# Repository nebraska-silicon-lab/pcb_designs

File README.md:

# PCB Designs for Silicon Lab

This repository contains design and related work for printed circuit boards used in Silicon Lab activites.

To edit these boards, install [Kicad](http://kicad-pcb.org/). Each design should have an PNG image of the most recent iteration of the design. This makes it easier to view the boards without needing to download and install Kicad.

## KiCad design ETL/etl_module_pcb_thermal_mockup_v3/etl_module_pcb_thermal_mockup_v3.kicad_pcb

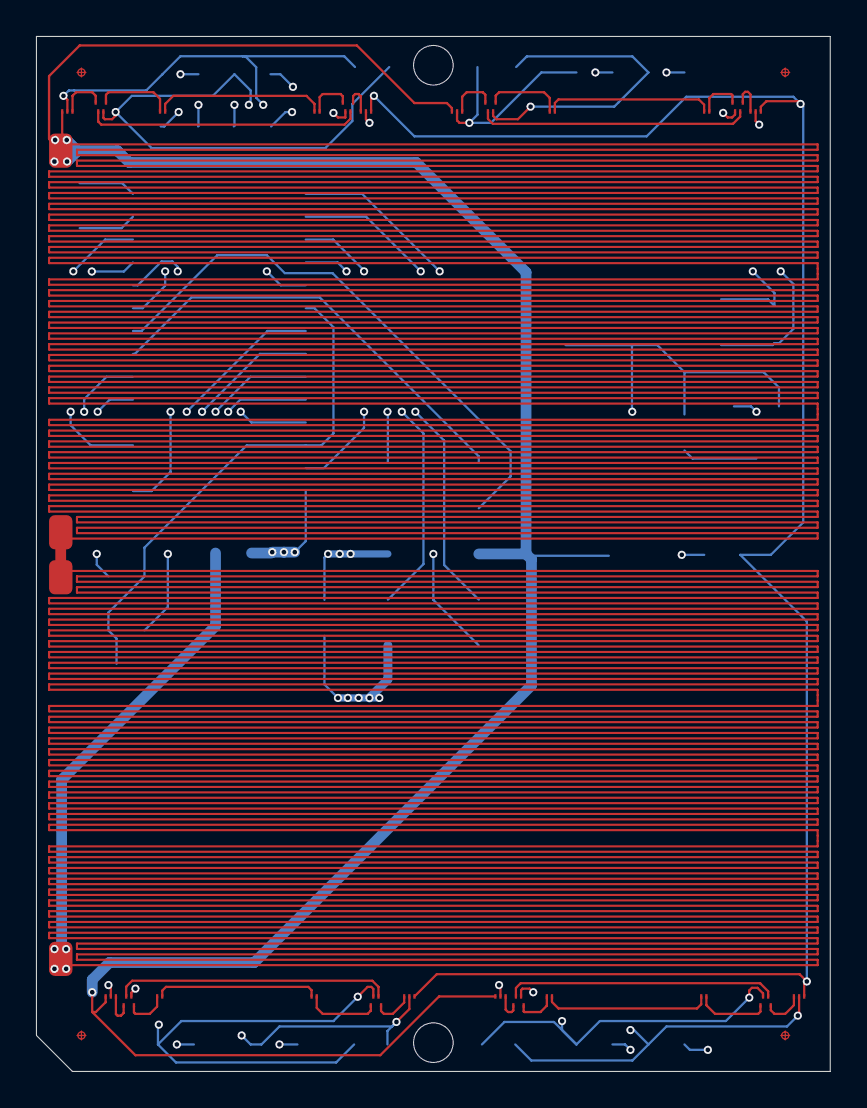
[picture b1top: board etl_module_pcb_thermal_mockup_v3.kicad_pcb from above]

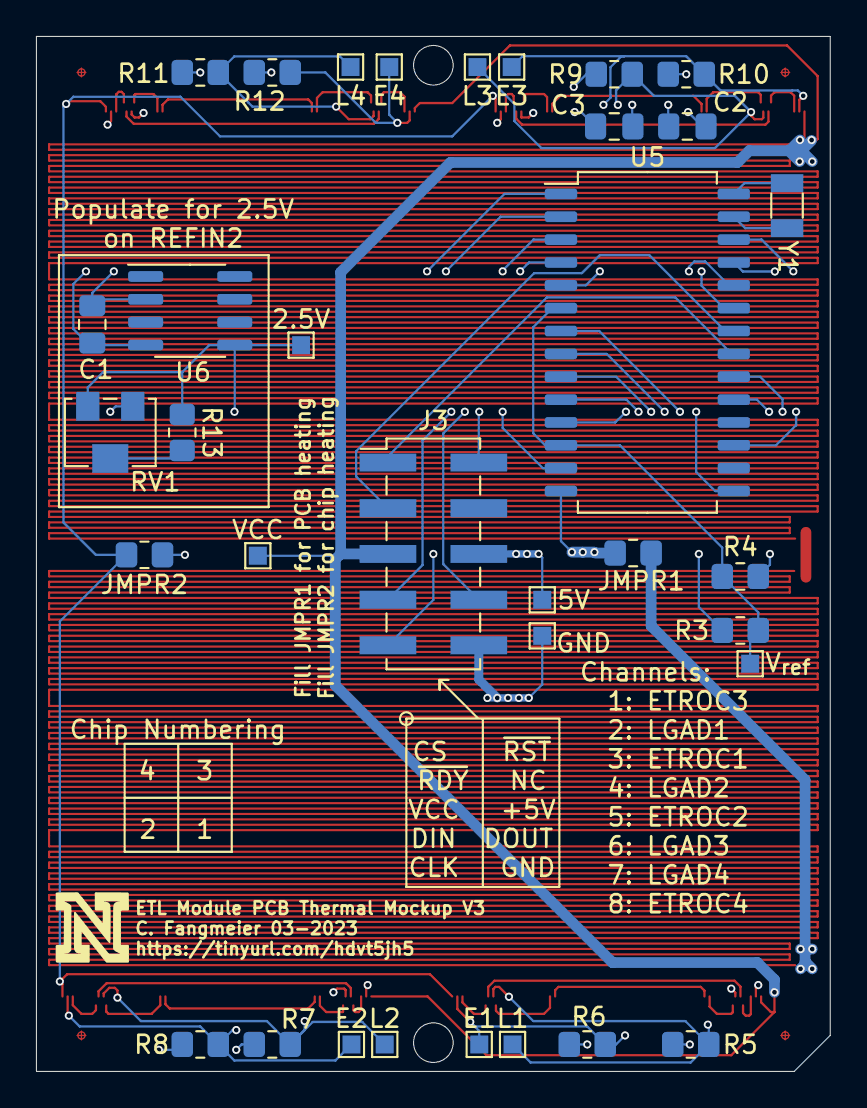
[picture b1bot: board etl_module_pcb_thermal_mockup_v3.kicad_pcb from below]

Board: 4 copper layers, 44.1 x 57.5 mm, 40 parts (34 on the bottom side), 49 nets.

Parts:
2.5V, 5V: TestPoint; TestPoint_Pad_1.0x1.0mm
C1: 1uF; C_0805_2012Metric_Pad1.18x1.45mm_HandSolder
C2: 0.1uF; C_0805_2012Metric_Pad1.18x1.45mm_HandSolder
C3: 10 uF; C_0805_2012Metric_Pad1.18x1.45mm_HandSolder
E1, E2, E3, E4: TestPoint; TestPoint_Pad_1.0x1.0mm
GND: TestPoint; TestPoint_Pad_1.0x1.0mm
J3: Conn_02x05_Counter_Clockwise; PinHeader_2x05_P2.54mm_Vertical_SMD
JMPR1, JMPR2: 0; R_0805_2012Metric_Pad1.20x1.40mm_HandSolder
L1, L2, L3, L4: TestPoint; TestPoint_Pad_1.0x1.0mm
R1, R2: 12.6; ETROC_Heater_Serpantine
R3, R4, R5, R6, R7, R8, R9, R10, R11, R12: 40k; R_0805_2012Metric_Pad1.20x1.40mm_HandSolder
R13: 1M; R_0805_2012Metric_Pad1.20x1.40mm_HandSolder
RV1: 25k; Potentiometer_Bourns_3224W_Vertical
U1, U2, U3, U4: ETROC_dummy_thermal_sensors; PCB_ETROC2_dummy
U5: AD77x8; SOIC-28W_7.5x18.7mm_P1.27mm
U6: AD780; SOIC-8_3.9x4.9mm_P1.27mm
VCC: TestPoint; TestPoint_Pad_1.0x1.0mm
V_{ref}: TestPoint; TestPoint_Pad_1.0x1.0mm
Y1: 32kHz; Crystal_SMD_3215-2Pin_3.2x1.5mm

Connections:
+5V: 5V.1, C1.1, C2.1, C3.1, J3.6, R3.1, R5.1, R6.1, R7.1, R8.1, R9.1, R10.1, R11.1, R12.1, U5.3 (AV_{DD}), U5.26 (DV_{DD}), U6.2 (+V_{IN})
/2.5V: 2.5V.1, R13.1, RV1.3, U5.13 (REFIN2(+)/AIN9), U6.5 (TRIM)
/CLK: J3.9, U5.20 (SCLK)
/CS: J3.1, U5.21 (~CS)
/DIN: J3.7, U5.24 (DIN)
/DOUT: J3.8, U5.23 (DOUT)
/ETROC1: E1.1, R6.2, U1.119 (ETROC_BR-), U5.9 (AIN3)
/ETROC2: E2.1, R8.2, U2.119 (ETROC_BR-), U5.11 (AIN5)
/ETROC3: E3.1, R10.2, U3.119 (ETROC_BR-), U5.7 (AIN1)
/ETROC4: E4.1, R12.2, U4.119 (ETROC_BR-), U5.2 (AIN8)
/LGAD1: L1.1, R5.2, U1.105 (LGAD_BR-), U5.8 (AIN2)
/LGAD2: L2.1, R7.2, U2.105 (LGAD_BR-), U5.10 (AIN4)
/LGAD3: L3.1, R9.2, U3.105 (LGAD_BR-), U5.15 (AIN6)
/LGAD4: L4.1, R11.2, U4.105 (LGAD_BR-), U5.1 (AIN7)
/VSS: JMPR2.2, U1.121 (VSS), U2.121 (VSS), U3.1 (VCC), U4.1 (VCC)
/V_{ref}: R3.2, R4.1, U5.6 (REFIN1(+)), U5.12 (AINCOM), V_{ref}.1
/~RDY: J3.3, U5.22 (~RDY)
/~RESET: J3.2, U5.19 (~RESET)
GND: C1.2, C2.2, C3.2, GND.1, J3.10, JMPR1.2, JMPR2.1, R4.2, RV1.1, U1.3 (ETROC_BLp), U1.11 (LGAD_BL+), U2.3 (ETROC_BLp), U2.11 (LGAD_BL+), U3.3 (ETROC_BLp), U3.11 (LGAD_BL+), U4.3 (ETROC_BLp), U4.11 (LGAD_BL+), U5.4 (AGND), U5.5 (REFIN1(-)), U5.14 (REFIN2(-)/AIN10), U5.17 (AGND), U5.25 (DGND), U6.4 (GND)
unnamed: JMPR1.1, R2.2
unnamed: R1.2, R2.1
unnamed: R13.2, RV1.2
unnamed: U1.5 (ETROC_BL-), U1.8 (ETROC_TL+)
unnamed: U1.12 (LGAD_BL-), U1.21 (LGAD_TL+)
unnamed: U1.23 (LGAD_TL-), U1.81 (LGAD_TR+)
unnamed: U1.83 (LGAD_TR-), U1.104 (LGAD_BR+)
unnamed: U1.9 (ETROC_TL-), U1.107 (ETROC_TR+)
unnamed: U1.108 (ETROC_TR-), U1.117 (ETROC_BR+)
unnamed: U2.5 (ETROC_BL-), U2.8 (ETROC_TL+)
unnamed: U2.12 (LGAD_BL-), U2.21 (LGAD_TL+)
unnamed: U2.23 (LGAD_TL-), U2.81 (LGAD_TR+)
unnamed: U2.83 (LGAD_TR-), U2.104 (LGAD_BR+)
unnamed: U2.9 (ETROC_TL-), U2.107 (ETROC_TR+)
unnamed: U2.108 (ETROC_TR-), U2.117 (ETROC_BR+)
unnamed: U3.5 (ETROC_BL-), U3.8 (ETROC_TL+)
unnamed: U3.12 (LGAD_BL-), U3.21 (LGAD_TL+)
unnamed: U3.23 (LGAD_TL-), U3.81 (LGAD_TR+)
unnamed: U3.83 (LGAD_TR-), U3.104 (LGAD_BR+)
unnamed: U3.9 (ETROC_TL-), U3.107 (ETROC_TR+)
unnamed: U3.108 (ETROC_TR-), U3.117 (ETROC_BR+)
unnamed: U4.5 (ETROC_BL-), U4.8 (ETROC_TL+)
unnamed: U4.12 (LGAD_BL-), U4.21 (LGAD_TL+)
unnamed: U4.23 (LGAD_TL-), U4.81 (LGAD_TR+)
unnamed: U4.83 (LGAD_TR-), U4.104 (LGAD_BR+)
unnamed: U4.9 (ETROC_TL-), U4.107 (ETROC_TR+)
unnamed: U4.108 (ETROC_TR-), U4.117 (ETROC_BR+)
unnamed: U5.27 (XTAL2), Y1.1
unnamed: U5.28 (XTAL1), Y1.2
VCC: J3.5, R1.1, U1.1 (VCC), U2.1 (VCC), U3.121 (VSS), U4.121 (VSS), VCC.1

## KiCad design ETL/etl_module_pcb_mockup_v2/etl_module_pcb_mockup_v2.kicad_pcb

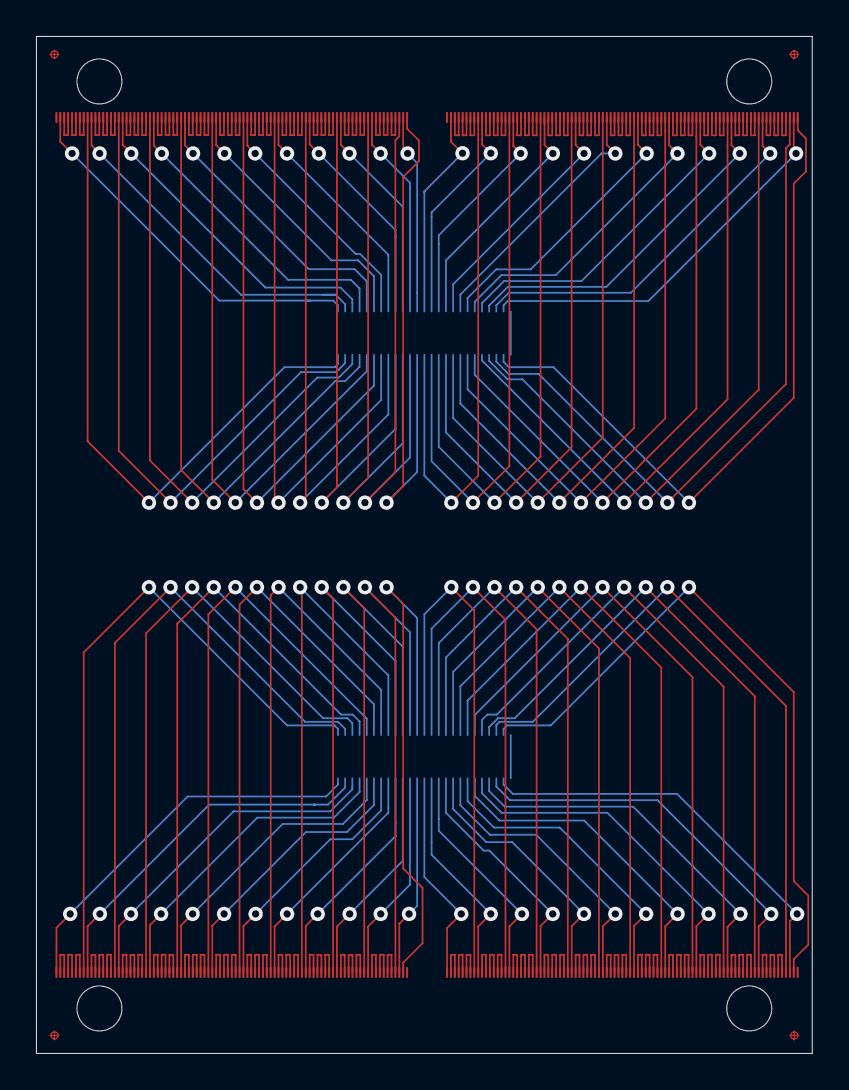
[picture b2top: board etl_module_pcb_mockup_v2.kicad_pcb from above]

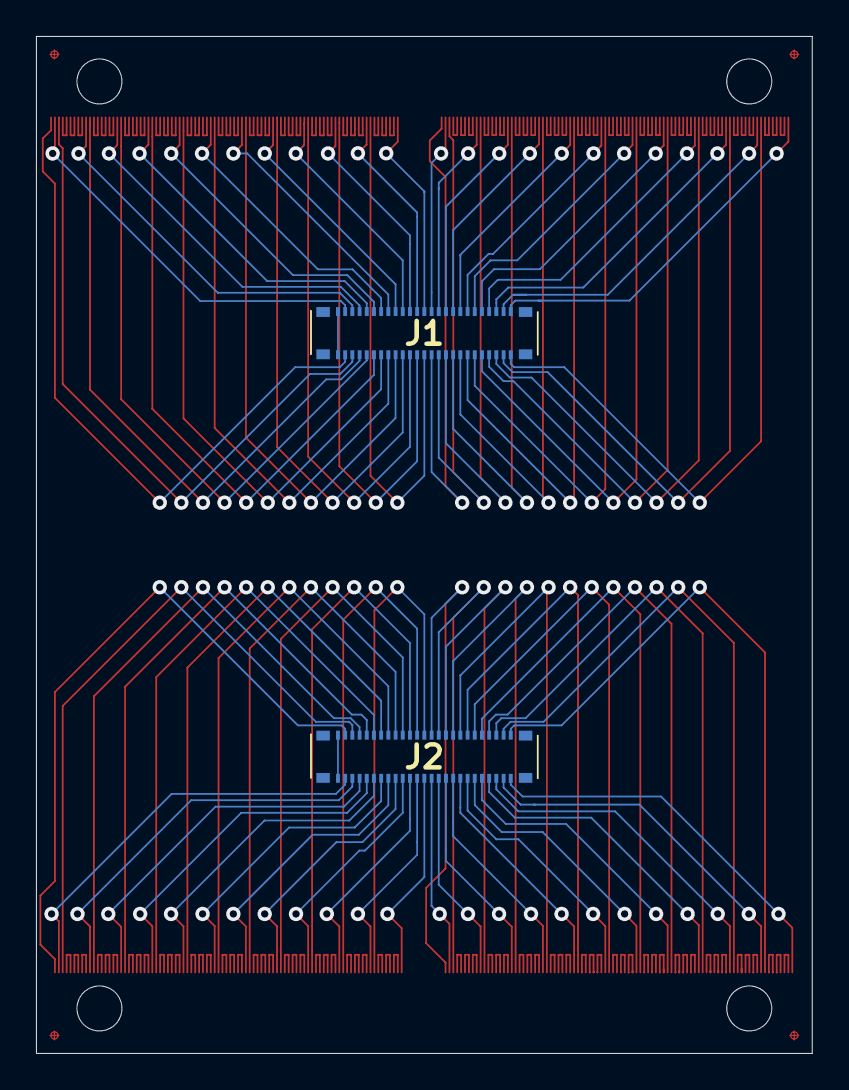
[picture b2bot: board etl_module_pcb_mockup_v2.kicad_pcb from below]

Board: 2 copper layers, 43.1 x 56.5 mm, 6 parts (2 on the bottom side), 230 nets.

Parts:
J1, J2: WP7B-S050VA1-R8000; WP7BS050VA1R8000
J3, J4, J5, J6: ETROC_91pad; ETROC_91pad_120x200um_216p44um_pitch

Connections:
/01_N: J2.1, J5.8
/01_P: J2.2, J5.1
/02_N: J2.3, J5.16
/02_P: J2.4, J5.9
/03_N: J2.5, J5.24
/03_P: J2.6, J5.17
/04_N: J2.7, J5.32
/04_P: J2.8, J5.25
/05_N: J2.9, J5.40
/05_P: J2.10, J5.33
/06_N: J2.11, J5.48
/06_P: J2.12, J5.41
/07_N: J2.13, J5.56
/07_P: J2.14, J5.49
/08_N: J2.15, J5.64
/08_P: J2.16, J5.57
/09_N: J2.17, J5.72
/09_P: J2.18, J5.65
/10_N: J2.19, J5.80
/10_P: J2.20, J5.73
/11_N: J2.21, J5.88
/11_P: J2.22, J5.81
/12_N: J2.23, J5.90
/12_P: J2.24, J5.89
/13_N: J2.25, J6.8
/13_P: J2.26, J6.1
/14_N: J2.27, J6.16
/14_P: J2.28, J6.9
/15_N: J2.29, J6.24
/15_P: J2.30, J6.17
/16_N: J2.31, J6.32
/16_P: J2.32, J6.25
/17_N: J2.33, J6.40
/17_P: J2.34, J6.33
/18_N: J2.35, J6.48
/18_P: J2.36, J6.41
/19_N: J2.37, J6.56
/19_P: J2.38, J6.49
/20_N: J2.39, J6.64
/20_P: J2.40, J6.57
/21_N: J2.41, J6.72
/21_P: J2.42, J6.65
/22_N: J2.43, J6.80
/22_P: J2.44, J6.73
/23_N: J2.45, J6.88
/23_P: J2.46, J6.81
/24_N: J2.47, J6.90
/24_P: J2.48, J6.89
/26_N: J1.2, J3.9
/26_P: J1.1, J3.2
/27_N: J1.4, J3.17
/27_P: J1.3, J3.10
/28_N: J1.6, J3.25
/28_P: J1.5, J3.18
/29_N: J1.8, J3.33
/29_P: J1.7, J3.26
/30_N: J1.10, J3.41
/30_P: J1.9, J3.34
/31_N: J1.12, J3.49
/31_P: J1.11, J3.42
/32_N: J1.14, J3.57
/32_P: J1.13, J3.50
/33_N: J1.16, J3.65
/33_P: J1.15, J3.58
/34_N: J1.18, J3.73
/34_P: J1.17, J3.66
/35_N: J1.20, J3.81
/35_P: J1.19, J3.74
/36_N: J1.22, J3.89
/36_P: J1.21, J3.82
/37_N: J1.24, J3.91
/37_P: J1.23, J3.90
/38_N: J1.26, J4.9
/38_P: J1.25, J4.2
/39_N: J1.28, J4.17
/39_P: J1.27, J4.10
/40_N: J1.30, J4.25
/40_P: J1.29, J4.18
/41_N: J1.32, J4.33
/41_P: J1.31, J4.26
/42_N: J1.34, J4.41
/42_P: J1.33, J4.34
/43_N: J1.36, J4.49
/43_P: J1.35, J4.42
/44_N: J1.38, J4.57
/44_P: J1.37, J4.50
/45_N: J1.40, J4.65
/45_P: J1.39, J4.58
/46_N: J1.42, J4.73
/46_P: J1.41, J4.66
/47_N: J1.44, J4.81
/47_P: J1.43, J4.74
/48_N: J1.46, J4.89
/48_P: J1.45, J4.82
/49_N: J1.48, J4.91
/49_P: J1.47, J4.90
/S1: J2.49, J2.50
/S2: J1.49, J1.50
unnamed: J3.3, J3.4
unnamed: J3.5, J3.6
unnamed: J3.7, J3.8
unnamed: J3.11, J3.12
unnamed: J3.13, J3.14
unnamed: J3.15, J3.16
unnamed: J3.19, J3.20
unnamed: J3.21, J3.22
unnamed: J3.23, J3.24
unnamed: J3.27, J3.28
unnamed: J3.29, J3.30
unnamed: J3.31, J3.32
unnamed: J3.35, J3.36
unnamed: J3.37, J3.38
unnamed: J3.39, J3.40
unnamed: J3.43, J3.44
unnamed: J3.45, J3.46
unnamed: J3.47, J3.48
unnamed: J3.51, J3.52
unnamed: J3.53, J3.54
unnamed: J3.55, J3.56
unnamed: J3.59, J3.60
unnamed: J3.61, J3.62
unnamed: J3.63, J3.64
unnamed: J3.67, J3.68
unnamed: J3.69, J3.70
unnamed: J3.71, J3.72
unnamed: J3.75, J3.76
unnamed: J3.77, J3.78
unnamed: J3.79, J3.80
unnamed: J3.83, J3.84
unnamed: J3.85, J3.86
unnamed: J3.87, J3.88
unnamed: J4.3, J4.4
unnamed: J4.5, J4.6
unnamed: J4.7, J4.8
unnamed: J4.11, J4.12
unnamed: J4.13, J4.14
unnamed: J4.15, J4.16
unnamed: J4.19, J4.20
unnamed: J4.21, J4.22
unnamed: J4.23, J4.24
unnamed: J4.27, J4.28
unnamed: J4.29, J4.30
unnamed: J4.31, J4.32
unnamed: J4.35, J4.36
unnamed: J4.37, J4.38
unnamed: J4.39, J4.40
unnamed: J4.43, J4.44
unnamed: J4.45, J4.46
unnamed: J4.47, J4.48
unnamed: J4.51, J4.52
unnamed: J4.53, J4.54
unnamed: J4.55, J4.56
unnamed: J4.59, J4.60
unnamed: J4.61, J4.62
unnamed: J4.63, J4.64
unnamed: J4.67, J4.68
unnamed: J4.69, J4.70
unnamed: J4.71, J4.72
unnamed: J4.75, J4.76
unnamed: J4.77, J4.78
unnamed: J4.79, J4.80
unnamed: J4.83, J4.84
unnamed: J4.85, J4.86
unnamed: J4.87, J4.88
unnamed: J5.2, J5.3
unnamed: J5.4, J5.5
unnamed: J5.6, J5.7
unnamed: J5.10, J5.11
unnamed: J5.12, J5.13
unnamed: J5.14, J5.15
unnamed: J5.18, J5.19
unnamed: J5.20, J5.21
unnamed: J5.22, J5.23
unnamed: J5.26, J5.27
unnamed: J5.28, J5.29
unnamed: J5.30, J5.31
unnamed: J5.34, J5.35
unnamed: J5.36, J5.37
unnamed: J5.38, J5.39
unnamed: J5.42, J5.43
unnamed: J5.44, J5.45
unnamed: J5.46, J5.47
unnamed: J5.50, J5.51
unnamed: J5.52, J5.53
unnamed: J5.54, J5.55
unnamed: J5.58, J5.59
unnamed: J5.60, J5.61
unnamed: J5.62, J5.63
unnamed: J5.66, J5.67
unnamed: J5.68, J5.69
unnamed: J5.70, J5.71
unnamed: J5.74, J5.75
unnamed: J5.76, J5.77
unnamed: J5.78, J5.79
unnamed: J5.82, J5.83
unnamed: J5.84, J5.85
unnamed: J5.86, J5.87
unnamed: J6.2, J6.3
unnamed: J6.4, J6.5
unnamed: J6.6, J6.7
unnamed: J6.10, J6.11
unnamed: J6.12, J6.13
unnamed: J6.14, J6.15
unnamed: J6.18, J6.19
unnamed: J6.20, J6.21
unnamed: J6.22, J6.23
unnamed: J6.26, J6.27
unnamed: J6.28, J6.29
unnamed: J6.30, J6.31
unnamed: J6.34, J6.35
unnamed: J6.36, J6.37
unnamed: J6.38, J6.39
unnamed: J6.42, J6.43
unnamed: J6.44, J6.45
unnamed: J6.46, J6.47
unnamed: J6.50, J6.51
unnamed: J6.52, J6.53
unnamed: J6.54, J6.55
unnamed: J6.58, J6.59
unnamed: J6.60, J6.61
unnamed: J6.62, J6.63
unnamed: J6.66, J6.67
unnamed: J6.68, J6.69
unnamed: J6.70, J6.71
unnamed: J6.74, J6.75
unnamed: J6.76, J6.77
unnamed: J6.78, J6.79
unnamed: J6.82, J6.83
unnamed: J6.84, J6.85
unnamed: J6.86, J6.87

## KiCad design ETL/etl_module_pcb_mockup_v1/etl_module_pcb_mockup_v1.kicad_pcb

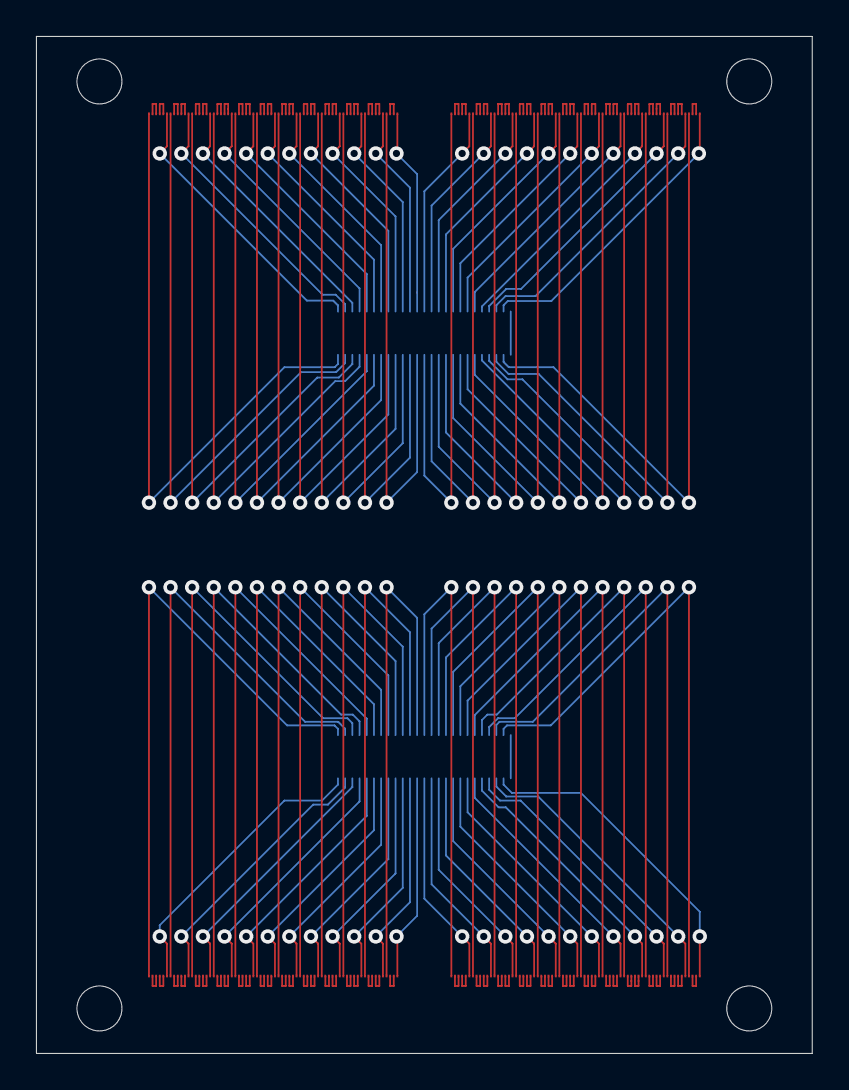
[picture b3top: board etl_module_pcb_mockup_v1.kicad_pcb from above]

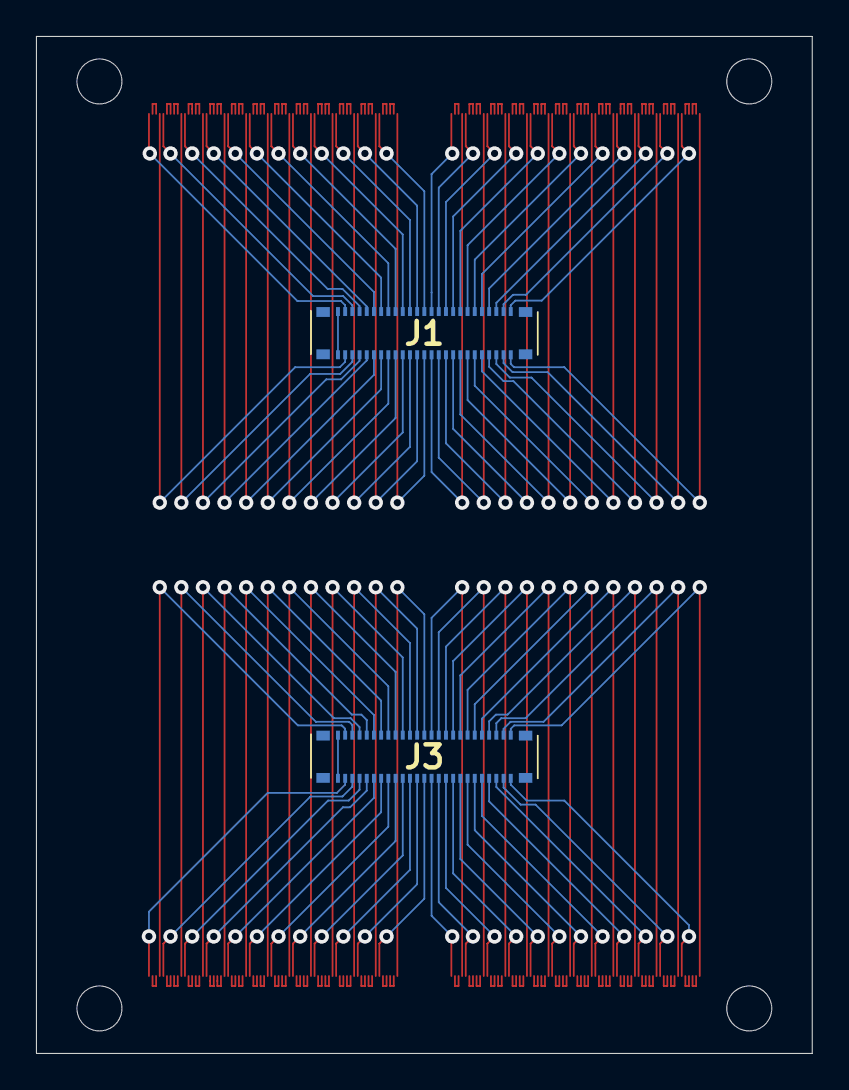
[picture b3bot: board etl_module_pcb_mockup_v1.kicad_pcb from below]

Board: 2 copper layers, 43.1 x 56.5 mm, 6 parts (2 on the bottom side), 190 nets.

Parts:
J1, J3: WP7B-S050VA1-R8000; WP7BS050VA1R8000
J2, J4, J5, J6: Conn_2Rows-71Pins; ETROC_70pad_100x150um_200um_pitch

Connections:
/01_A: J2.2, J2.3
/01_B: J2.4, J2.5
/01_N: J2.1, J3.1
/01_P: J2.6, J3.2
/02_A: J2.8, J2.9
/02_B: J2.10, J2.11
/02_N: J2.7, J3.3
/02_P: J2.12, J3.4
/03_A: J2.14, J2.15
/03_B: J2.16, J2.17
/03_N: J2.13, J3.5
/03_P: J2.18, J3.6
/04_A: J2.20, J2.21
/04_B: J2.22, J2.23
/04_N: J2.19, J3.7
/04_P: J2.24, J3.8
/05_A: J2.26, J2.27
/05_B: J2.28, J2.29
/05_N: J2.25, J3.9
/05_P: J2.30, J3.10
/06_A: J2.32, J2.33
/06_B: J2.34, J2.35
/06_N: J2.31, J3.11
/06_P: J2.36, J3.12
/07_A: J2.38, J2.39
/07_B: J2.40, J2.41
/07_N: J2.37, J3.13
/07_P: J2.42, J3.14
/08_A: J2.44, J2.45
/08_B: J2.46, J2.47
/08_N: J2.43, J3.15
/08_P: J2.48, J3.16
/09_A: J2.50, J2.51
/09_B: J2.52, J2.53
/09_N: J2.49, J3.17
/09_P: J2.54, J3.18
/10_A: J2.56, J2.57
/10_B: J2.58, J2.59
/10_N: J2.55, J3.19
/10_P: J2.60, J3.20
/11_A: J2.62, J2.63
/11_B: J2.64, J2.65
/11_N: J2.61, J3.21
/11_P: J2.66, J3.22
/12_A: J2.68, J2.69
/12_N: J2.67, J3.23
/12_P: J2.70, J3.24
/13_A: J4.2, J4.3
/13_B: J4.4, J4.5
/13_N: J3.25, J4.1
/13_P: J3.26, J4.6
/14_A: J4.8, J4.9
/14_B: J4.10, J4.11
/14_N: J3.27, J4.7
/14_P: J3.28, J4.12
/15_A: J4.14, J4.15
/15_B: J4.16, J4.17
/15_N: J3.29, J4.13
/15_P: J3.30, J4.18
/16_A: J4.20, J4.21
/16_B: J4.22, J4.23
/16_N: J3.31, J4.19
/16_P: J3.32, J4.24
/17_A: J4.26, J4.27
/17_B: J4.28, J4.29
/17_N: J3.33, J4.25
/17_P: J3.34, J4.30
/18_A: J4.32, J4.33
/18_B: J4.34, J4.35
/18_N: J3.35, J4.31
/18_P: J3.36, J4.36
/19_A: J4.38, J4.39
/19_B: J4.40, J4.41
/19_N: J3.37, J4.37
/19_P: J3.38, J4.42
/20_A: J4.44, J4.45
/20_B: J4.46, J4.47
/20_N: J3.39, J4.43
/20_P: J3.40, J4.48
/21_A: J4.50, J4.51
/21_B: J4.52, J4.53
/21_N: J3.41, J4.49
/21_P: J3.42, J4.54
/22_A: J4.56, J4.57
/22_B: J4.58, J4.59
/22_N: J3.43, J4.55
/22_P: J3.44, J4.60
/23_A: J4.62, J4.63
/23_B: J4.64, J4.65
/23_N: J3.45, J4.61
/23_P: J3.46, J4.66
/24_A: J4.68, J4.69
/24_N: J3.47, J4.67
/24_P: J3.48, J4.70
/26_A: J5.2, J5.3
/26_B: J5.4, J5.5
/26_N: J1.2, J5.1
/26_P: J1.1, J5.6
/27_A: J5.8, J5.9
/27_B: J5.10, J5.11
/27_N: J1.4, J5.7
/27_P: J1.3, J5.12
/28_A: J5.14, J5.15
/28_B: J5.16, J5.17
/28_N: J1.6, J5.13
/28_P: J1.5, J5.18
/29_A: J5.20, J5.21
/29_B: J5.22, J5.23
/29_N: J1.8, J5.19
/29_P: J1.7, J5.24
/30_A: J5.26, J5.27
/30_B: J5.28, J5.29
/30_N: J1.10, J5.25
/30_P: J1.9, J5.30
/31_A: J5.32, J5.33
/31_B: J5.34, J5.35
/31_N: J1.12, J5.31
/31_P: J1.11, J5.36
/32_A: J5.38, J5.39
/32_B: J5.40, J5.41
/32_N: J1.14, J5.37
/32_P: J1.13, J5.42
/33_A: J5.44, J5.45
/33_B: J5.46, J5.47
/33_N: J1.16, J5.43
/33_P: J1.15, J5.48
/34_A: J5.50, J5.51
/34_B: J5.52, J5.53
/34_N: J1.18, J5.49
/34_P: J1.17, J5.54
/35_A: J5.56, J5.57
/35_B: J5.58, J5.59
/35_N: J1.20, J5.55
/35_P: J1.19, J5.60
/36_A: J5.62, J5.63
/36_B: J5.64, J5.65
/36_N: J1.22, J5.61
/36_P: J1.21, J5.66
/37_A: J5.68, J5.69
/37_N: J1.24, J5.67
/37_P: J1.23, J5.70
/38_A: J6.2, J6.3
/38_B: J6.4, J6.5
/38_N: J1.26, J6.1
/38_P: J1.25, J6.6
/39_A: J6.8, J6.9
/39_B: J6.10, J6.11
/39_N: J1.28, J6.7
/39_P: J1.27, J6.12
/40_A: J6.14, J6.15
/40_B: J6.16, J6.17
/40_N: J1.30, J6.13
/40_P: J1.29, J6.18
/41_A: J6.20, J6.21
/41_B: J6.22, J6.23
/41_N: J1.32, J6.19
/41_P: J1.31, J6.24
/42_A: J6.26, J6.27
/42_B: J6.28, J6.29
/42_N: J1.34, J6.25
/42_P: J1.33, J6.30
/43_A: J6.32, J6.33
/43_B: J6.34, J6.35
/43_N: J1.36, J6.31
/43_P: J1.35, J6.36
/44_A: J6.38, J6.39
/44_B: J6.40, J6.41
/44_N: J1.38, J6.37
/44_P: J1.37, J6.42
/45_A: J6.44, J6.45
/45_B: J6.46, J6.47
/45_N: J1.40, J6.43
/45_P: J1.39, J6.48
/46_A: J6.50, J6.51
/46_B: J6.52, J6.53
/46_N: J1.42, J6.49
/46_P: J1.41, J6.54
/47_A: J6.56, J6.57
/47_B: J6.58, J6.59
/47_N: J1.44, J6.55
/47_P: J1.43, J6.60
/48_A: J6.62, J6.63
/48_B: J6.64, J6.65
/48_N: J1.46, J6.61
/48_P: J1.45, J6.66
/49_A: J6.68, J6.69
/49_N: J1.48, J6.67
/49_P: J1.47, J6.70
/S1: J3.49, J3.50
/S2: J1.49, J1.50

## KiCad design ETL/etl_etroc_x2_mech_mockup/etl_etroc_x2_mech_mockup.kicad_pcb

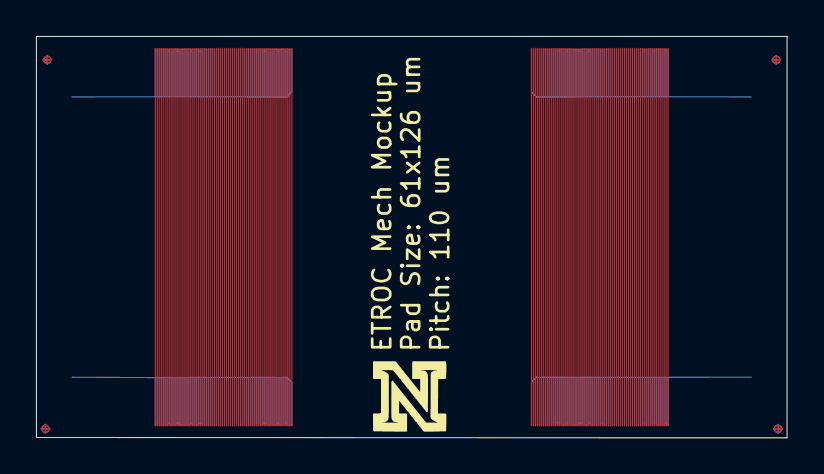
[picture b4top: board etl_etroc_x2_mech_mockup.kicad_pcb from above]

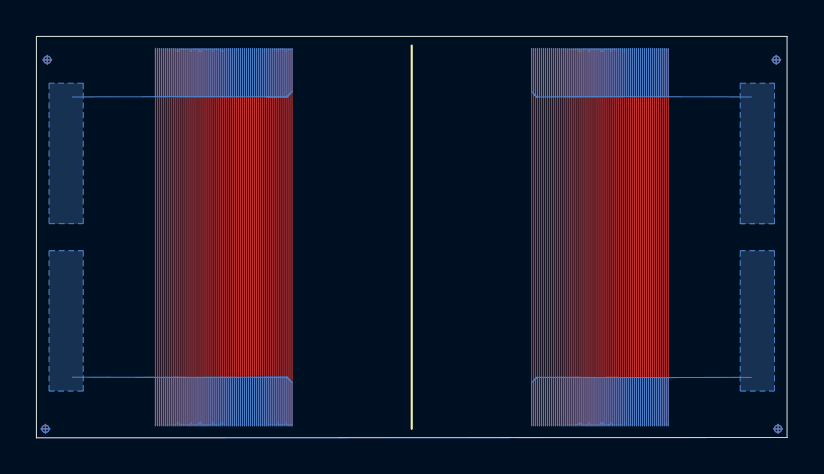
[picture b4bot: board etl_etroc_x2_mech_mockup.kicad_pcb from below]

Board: 2 copper layers, 41.7 x 22.3 mm, 8 parts (4 on the bottom side), 144 nets.

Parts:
J1, J2, J3, J4, J5, J6, J7, J8: Conn_02x35_Top_Bottom; ETROC_70pad_61x126um_110um_pitch

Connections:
/BOT_GRP1: J5.1, J5.2, J5.3, J5.4, J5.5, J5.6, J5.7, J5.8, J5.9, J5.10, J5.11, J5.12, J5.13, J5.14, J5.15, J5.16, J5.17, J5.18, J5.19, J5.20, J5.21, J5.22, J5.23, J5.24, J5.25, J5.26, J5.27, J5.28, J5.29, J5.30, J5.31, J5.32, J5.33, J5.34, J5.35, J5.36, J5.37, J5.38, J5.39, J5.40, J5.41, J5.42, J5.43, J5.44, J5.45, J5.46, J5.47, J5.48, J5.49, J5.50, J5.51, J5.52, J5.53, J5.54, J5.55, J5.56, J5.57, J5.58, J5.59, J5.60, J5.61, J5.62, J5.63, J5.64, J5.65, J5.66, J5.67, J5.68, J5.69, J5.70
/BOT_GRP2: J6.1, J6.2, J6.3, J6.4, J6.5, J6.6, J6.7, J6.8, J6.9, J6.10, J6.11, J6.12, J6.13, J6.14, J6.15, J6.16, J6.17, J6.18, J6.19, J6.20, J6.21, J6.22, J6.23, J6.24, J6.25, J6.26, J6.27, J6.28, J6.29, J6.30, J6.31, J6.32, J6.33, J6.34, J6.35, J6.36, J6.37, J6.38, J6.39, J6.40, J6.41, J6.42, J6.43, J6.44, J6.45, J6.46, J6.47, J6.48, J6.49, J6.50, J6.51, J6.52, J6.53, J6.54, J6.55, J6.56, J6.57, J6.58, J6.59, J6.60, J6.61, J6.62, J6.63, J6.64, J6.65, J6.66, J6.67, J6.68, J6.69, J6.70
/BOT_GRP3: J7.1, J7.2, J7.3, J7.4, J7.5, J7.6, J7.7, J7.8, J7.9, J7.10, J7.11, J7.12, J7.13, J7.14, J7.15, J7.16, J7.17, J7.18, J7.19, J7.20, J7.21, J7.22, J7.23, J7.24, J7.25, J7.26, J7.27, J7.28, J7.29, J7.30, J7.31, J7.32, J7.33, J7.34, J7.35, J7.36, J7.37, J7.38, J7.39, J7.40, J7.41, J7.42, J7.43, J7.44, J7.45, J7.46, J7.47, J7.48, J7.49, J7.50, J7.51, J7.52, J7.53, J7.54, J7.55, J7.56, J7.57, J7.58, J7.59, J7.60, J7.61, J7.62, J7.63, J7.64, J7.65, J7.66, J7.67, J7.68, J7.69, J7.70
/BOT_GRP4: J8.1, J8.2, J8.3, J8.4, J8.5, J8.6, J8.7, J8.8, J8.9, J8.10, J8.11, J8.12, J8.13, J8.14, J8.15, J8.16, J8.17, J8.18, J8.19, J8.20, J8.21, J8.22, J8.23, J8.24, J8.25, J8.26, J8.27, J8.28, J8.29, J8.30, J8.31, J8.32, J8.33, J8.34, J8.35, J8.36, J8.37, J8.38, J8.39, J8.40, J8.41, J8.42, J8.43, J8.44, J8.45, J8.46, J8.47, J8.48, J8.49, J8.50, J8.51, J8.52, J8.53, J8.54, J8.55, J8.56, J8.57, J8.58, J8.59, J8.60, J8.61, J8.62, J8.63, J8.64, J8.65, J8.66, J8.67, J8.68, J8.69, J8.70
/TOP_A1: J1.1, J3.1
/TOP_A2: J1.2, J3.2
/TOP_A3: J1.3, J3.3
/TOP_A4: J1.4, J3.4
/TOP_A5: J1.5, J3.5
/TOP_A6: J1.6, J3.6
/TOP_A7: J1.7, J3.7
/TOP_A8: J1.8, J3.8
/TOP_A9: J1.9, J3.9
/TOP_A10: J1.10, J3.10
/TOP_A11: J1.11, J3.11
/TOP_A12: J1.12, J3.12
/TOP_A13: J1.13, J3.13
/TOP_A14: J1.14, J3.14
/TOP_A15: J1.15, J3.15
/TOP_A16: J1.16, J3.16
/TOP_A17: J1.17, J3.17
/TOP_A18: J1.18, J3.18
/TOP_A19: J1.19, J3.19
/TOP_A20: J1.20, J3.20
/TOP_A21: J1.21, J3.21
/TOP_A22: J1.22, J3.22
/TOP_A23: J1.23, J3.23
/TOP_A24: J1.24, J3.24
/TOP_A25: J1.25, J3.25
/TOP_A26: J1.26, J3.26
/TOP_A27: J1.27, J3.27
/TOP_A28: J1.28, J3.28
/TOP_A29: J1.29, J3.29
/TOP_A30: J1.30, J3.30
/TOP_A31: J1.31, J3.31
/TOP_A32: J1.32, J3.32
/TOP_A33: J1.33, J3.33
/TOP_A34: J1.34, J3.34
/TOP_A35: J1.35, J3.35
/TOP_A36: J1.36, J3.36
/TOP_A37: J1.37, J3.37
/TOP_A38: J1.38, J3.38
/TOP_A39: J1.39, J3.39
/TOP_A40: J1.40, J3.40
/TOP_A41: J1.41, J3.41
/TOP_A42: J1.42, J3.42
/TOP_A43: J1.43, J3.43
/TOP_A44: J1.44, J3.44
/TOP_A45: J1.45, J3.45
/TOP_A46: J1.46, J3.46
/TOP_A47: J1.47, J3.47
/TOP_A48: J1.48, J3.48
/TOP_A49: J1.49, J3.49
/TOP_A50: J1.50, J3.50
/TOP_A51: J1.51, J3.51
/TOP_A52: J1.52, J3.52
/TOP_A53: J1.53, J3.53
/TOP_A54: J1.54, J3.54
/TOP_A55: J1.55, J3.55
/TOP_A56: J1.56, J3.56
/TOP_A57: J1.57, J3.57
/TOP_A58: J1.58, J3.58
/TOP_A59: J1.59, J3.59
/TOP_A60: J1.60, J3.60
/TOP_A61: J1.61, J3.61
/TOP_A62: J1.62, J3.62
/TOP_A63: J1.63, J3.63
/TOP_A64: J1.64, J3.64
/TOP_A65: J1.65, J3.65
/TOP_A66: J1.66, J3.66
/TOP_A67: J1.67, J3.67
/TOP_A68: J1.68, J3.68
/TOP_A69: J1.69, J3.69
/TOP_A70: J1.70, J3.70
/TOP_B1: J2.1, J4.1
/TOP_B2: J2.2, J4.2
/TOP_B3: J2.3, J4.3
/TOP_B4: J2.4, J4.4
/TOP_B5: J2.5, J4.5
/TOP_B6: J2.6, J4.6
/TOP_B7: J2.7, J4.7
/TOP_B8: J2.8, J4.8
/TOP_B9: J2.9, J4.9
/TOP_B10: J2.10, J4.10
/TOP_B11: J2.11, J4.11
/TOP_B12: J2.12, J4.12
/TOP_B13: J2.13, J4.13
/TOP_B14: J2.14, J4.14
/TOP_B15: J2.15, J4.15
/TOP_B16: J2.16, J4.16
/TOP_B17: J2.17, J4.17
/TOP_B18: J2.18, J4.18
/TOP_B19: J2.19, J4.19
/TOP_B20: J2.20, J4.20
/TOP_B21: J2.21, J4.21
/TOP_B22: J2.22, J4.22
/TOP_B23: J2.23, J4.23
/TOP_B24: J2.24, J4.24
/TOP_B25: J2.25, J4.25
/TOP_B26: J2.26, J4.26
/TOP_B27: J2.27, J4.27
/TOP_B28: J2.28, J4.28
/TOP_B29: J2.29, J4.29
/TOP_B30: J2.30, J4.30
/TOP_B31: J2.31, J4.31
/TOP_B32: J2.32, J4.32
/TOP_B33: J2.33, J4.33
/TOP_B34: J2.34, J4.34
/TOP_B35: J2.35, J4.35
/TOP_B36: J2.36, J4.36
/TOP_B37: J2.37, J4.37
/TOP_B38: J2.38, J4.38
/TOP_B39: J2.39, J4.39
/TOP_B40: J2.40, J4.40
/TOP_B41: J2.41, J4.41
/TOP_B42: J2.42, J4.42
/TOP_B43: J2.43, J4.43
/TOP_B44: J2.44, J4.44
/TOP_B45: J2.45, J4.45
/TOP_B46: J2.46, J4.46
/TOP_B47: J2.47, J4.47
/TOP_B48: J2.48, J4.48
/TOP_B49: J2.49, J4.49
/TOP_B50: J2.50, J4.50
/TOP_B51: J2.51, J4.51
/TOP_B52: J2.52, J4.52
/TOP_B53: J2.53, J4.53
/TOP_B54: J2.54, J4.54
/TOP_B55: J2.55, J4.55
/TOP_B56: J2.56, J4.56
/TOP_B57: J2.57, J4.57
/TOP_B58: J2.58, J4.58
/TOP_B59: J2.59, J4.59
/TOP_B60: J2.60, J4.60
/TOP_B61: J2.61, J4.61
/TOP_B62: J2.62, J4.62
/TOP_B63: J2.63, J4.63
/TOP_B64: J2.64, J4.64
/TOP_B65: J2.65, J4.65
/TOP_B66: J2.66, J4.66
/TOP_B67: J2.67, J4.67
/TOP_B68: J2.68, J4.68
/TOP_B69: J2.69, J4.69
/TOP_B70: J2.70, J4.70

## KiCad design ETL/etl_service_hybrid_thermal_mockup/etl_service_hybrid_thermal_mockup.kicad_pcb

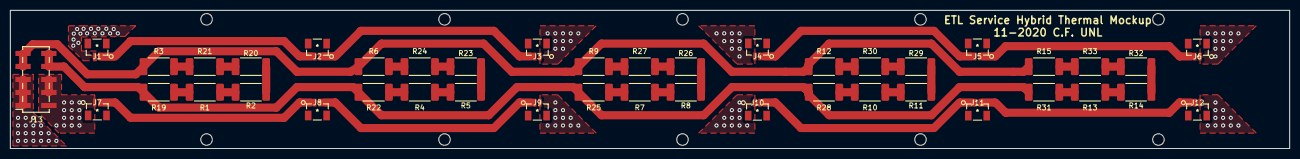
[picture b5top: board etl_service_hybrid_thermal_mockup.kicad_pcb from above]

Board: 4 copper layers, 250.0 x 27.0 mm, 43 parts (0 on the bottom side), 37 nets.

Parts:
J1, J2, J3, J4, J5, J6, J7, J8, J9, J10, J11, J12: Conn_01x02_Male; BM02B-SRSS-TB LFSN
J13: Conn_02x05_Odd_Even; PinSocket_2x05_P2.54mm_Vertical_SMD
R1, R2, R3, R4, R5, R6, R7, R8, R9, R10, R11, R12, R13, R14, R15, R19, R20, R21, R22, R23, R24, R25, R26, R27, R28, R29, R30, R31, R32, R33: 91; R_2512_6332Metric_Pad1.52x3.35mm_HandSolder

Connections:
/MOD_NEG: J3.1, J6.1, J9.2, J12.2, J13.1, J13.3, J13.5
/MOD_POS: J1.2, J4.2, J7.1, J10.1, J13.2, J13.4, J13.6
/SH_NEG: J13.7, J13.9, R3.2, R6.2, R9.2, R12.2, R15.2
/SH_POS: J13.8, J13.10, R19.1, R22.1, R25.1, R28.1, R31.1
unnamed: J1.1, J2.2
unnamed: J2.1, J3.2
unnamed: J4.1, J5.2
unnamed: J5.1, J6.2
unnamed: J7.2, J8.1
unnamed: J8.2, J9.1
unnamed: J10.2, J11.1
unnamed: J11.2, J12.1
unnamed: R1.1, R19.2
unnamed: R1.2, R2.2
unnamed: R2.1, R20.2
unnamed: R4.2, R5.2
unnamed: R7.2, R8.2
unnamed: R10.1, R28.2
unnamed: R10.2, R11.2
unnamed: R11.1, R29.2
unnamed: R12.1, R30.2
unnamed: R13.1, R31.2
unnamed: R13.2, R14.2
unnamed: R14.1, R32.2
unnamed: R15.1, R33.2
unnamed: R20.1, R21.1
unnamed: R3.1, R21.2
unnamed: R4.1, R22.2
unnamed: R23.1, R24.1
unnamed: R5.1, R23.2
unnamed: R6.1, R24.2
unnamed: R7.1, R25.2
unnamed: R26.1, R27.1
unnamed: R8.1, R26.2
unnamed: R9.1, R27.2
unnamed: R29.1, R30.1
unnamed: R32.1, R33.1

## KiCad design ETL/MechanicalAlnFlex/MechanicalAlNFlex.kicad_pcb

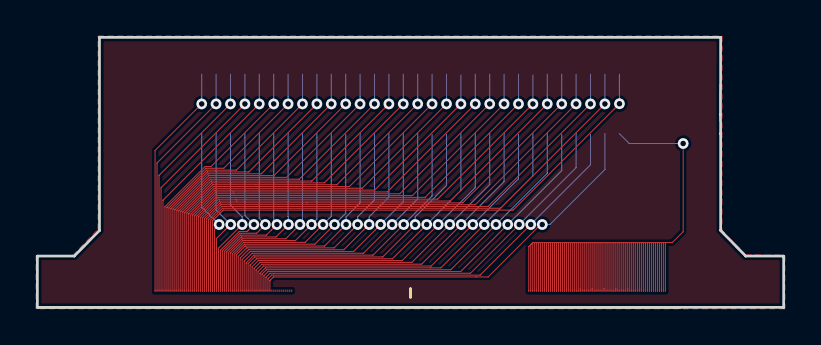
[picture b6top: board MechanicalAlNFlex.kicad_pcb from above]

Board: 2 copper layers, 41.5 x 15.0 mm, 3 parts (0 on the bottom side), 60 nets.

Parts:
J1: Conn_02x30_Odd_Even; SAMTEC_FTE-130-01-G-DV-EC
J2, J3: Conn_02x35_Top_Bottom; ETROC_70pad_61x126um_110um_pitch

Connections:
/COM: J1.1, J3.1, J3.2, J3.3, J3.4, J3.5, J3.6, J3.7, J3.8, J3.9, J3.10, J3.11, J3.12, J3.13, J3.14, J3.15, J3.16, J3.17, J3.18, J3.19, J3.20, J3.21, J3.22, J3.23, J3.24, J3.25, J3.26, J3.27, J3.28, J3.29, J3.30, J3.31, J3.32, J3.33, J3.34, J3.35, J3.36, J3.37, J3.38, J3.39, J3.40, J3.41, J3.42, J3.43, J3.44, J3.45, J3.46, J3.47, J3.48, J3.49, J3.50, J3.51, J3.52, J3.53, J3.54, J3.55, J3.56, J3.57, J3.58, J3.59, J3.60, J3.61, J3.62, J3.63, J3.64, J3.65, J3.66, J3.67, J3.68, J3.69, J3.70
/P1: J1.60, J2.1
/P2: J1.58, J2.2
/P3: J1.56, J2.3
/P4: J1.54, J2.4
/P5: J1.52, J2.5
/P6: J1.50, J2.6
/P7: J1.48, J2.7
/P8: J1.46, J2.8
/P9: J1.44, J2.9
/P10: J1.42, J2.10
/P11: J1.40, J2.11
/P12: J1.38, J2.12
/P13: J1.36, J2.13
/P14: J1.34, J2.14
/P15: J1.32, J2.15
/P16: J1.30, J2.16
/P17: J1.28, J2.17
/P18: J1.26, J2.18
/P19: J1.24, J2.19
/P20: J1.22, J2.20
/P21: J1.20, J2.21
/P22: J1.18, J2.22
/P23: J1.16, J2.23
/P24: J1.14, J2.24
/P25: J1.12, J2.25
/P26: J1.10, J2.26
/P27: J1.8, J2.27
/P28: J1.6, J2.28
/P29: J1.4, J2.29
/P30: J1.2, J2.30
/P31: J1.59, J2.31
/P32: J1.57, J2.32
/P33: J1.55, J2.33
/P34: J1.53, J2.34
/P35: J1.51, J2.35
/P36: J1.49, J2.36
/P37: J1.47, J2.37
/P38: J1.45, J2.38
/P39: J1.43, J2.39
/P40: J1.41, J2.40
/P41: J1.39, J2.41
/P42: J1.37, J2.42
/P43: J1.35, J2.43
/P44: J1.33, J2.44
/P45: J1.31, J2.45
/P46: J1.29, J2.46
/P47: J1.27, J2.47
/P48: J1.25, J2.48
/P49: J1.23, J2.49
/P50: J1.21, J2.50
/P51: J1.19, J2.51
/P52: J1.17, J2.52
/P53: J1.15, J2.53
/P54: J1.13, J2.54
/P55: J1.11, J2.55
/P56: J1.9, J2.56
/P57: J1.7, J2.57
/P58: J1.5, J2.58
/P59: J1.3, J2.59

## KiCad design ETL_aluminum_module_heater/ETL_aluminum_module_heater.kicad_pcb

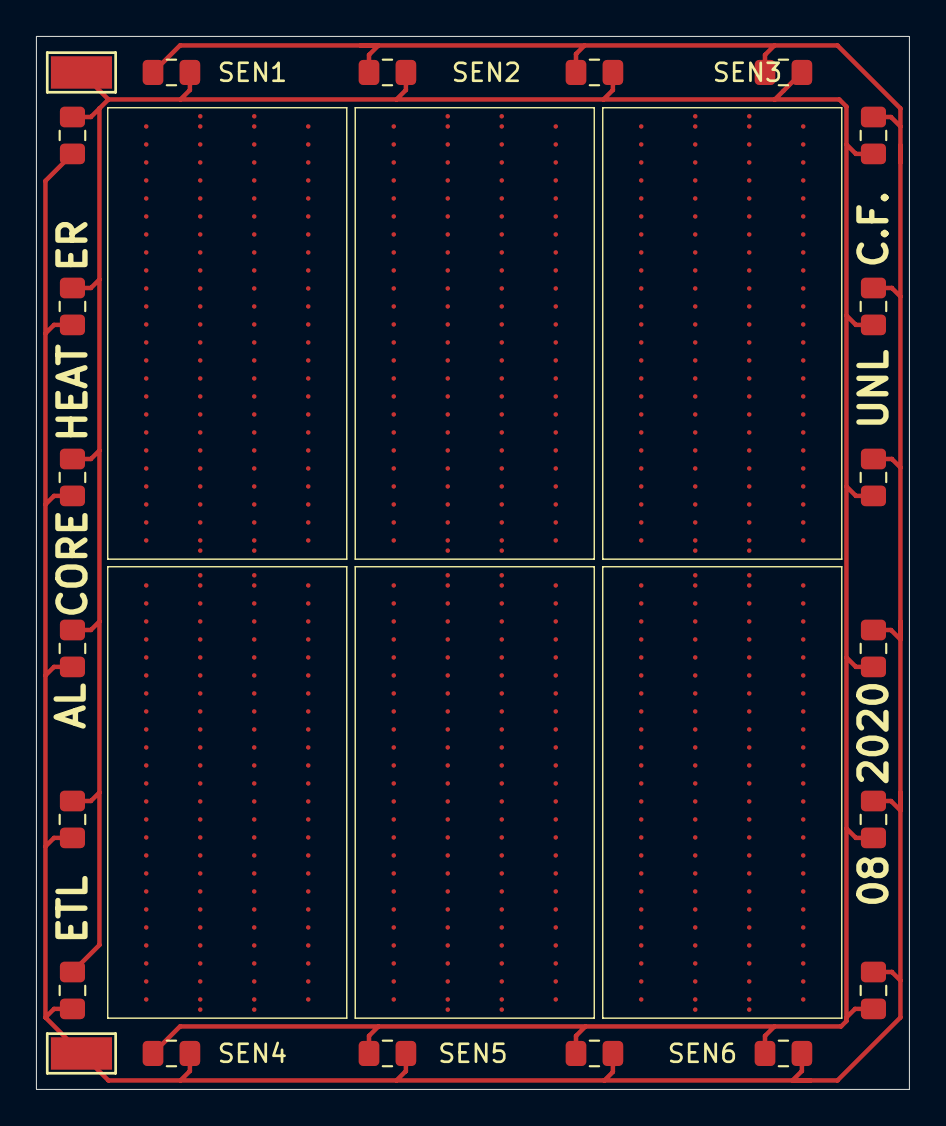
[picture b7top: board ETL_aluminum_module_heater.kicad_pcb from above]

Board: 2 copper layers, 48.5 x 58.5 mm, 28 parts (0 on the bottom side), 2 nets.

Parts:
J1, J2: Conn_01x01; TestPoint_Keystone_5015_Micro-Minature
R1, R2, R3, R4, R5, R6, R7, R8, R9, R10, R11, R12, R13, R14, R15, R16, R17, R18, R19, R20: 50; R_0805_2012Metric_Pad1.15x1.40mm_HandSolder
SEN1, SEN2, SEN3, SEN4, SEN5, SEN6: ROC1_sans_wirebonds

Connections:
/GND: J2.1, R1.1, R2.1, R3.1, R4.1, R5.1, R6.1, R7.1, R8.1, R9.1, R10.1, R11.2, R12.2, R13.2, R14.2, R15.2, R16.2, R17.2, R18.2, R19.2, R20.2
/VCC: J1.1, R1.2, R2.2, R3.2, R4.2, R5.2, R6.2, R7.2, R8.2, R9.2, R10.2, R11.1, R12.1, R13.1, R14.1, R15.1, R16.1, R17.1, R18.1, R19.1, R20.1

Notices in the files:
parts and their libraries:
Copyright 2016 Accelerated Designs. All rights reserved.
